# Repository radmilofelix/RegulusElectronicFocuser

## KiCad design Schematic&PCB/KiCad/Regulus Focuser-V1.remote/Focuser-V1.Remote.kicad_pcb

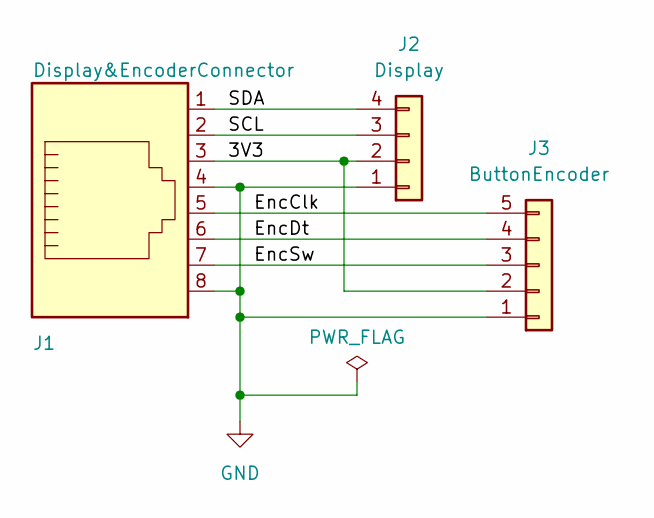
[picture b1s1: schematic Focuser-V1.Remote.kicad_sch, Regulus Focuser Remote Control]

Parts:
J1: Display&EncoderConnector; RJ45_Amphenol_54602-x08_Horizontal
J2: Display; PinHeader_1x04_P2.54mm_Vertical
J3: ButtonEncoder; PinHeader_1x05_P2.54mm_Vertical

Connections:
/3V3: J1.3, J2.2, J3.2
/EncClk: J1.5, J3.5
/EncDt: J1.6, J3.4
/EncSw: J1.7, J3.3
/SCL: J1.2, J2.3
/SDA: J1.1, J2.4
GND: J1.4, J1.8, J2.1, J3.1

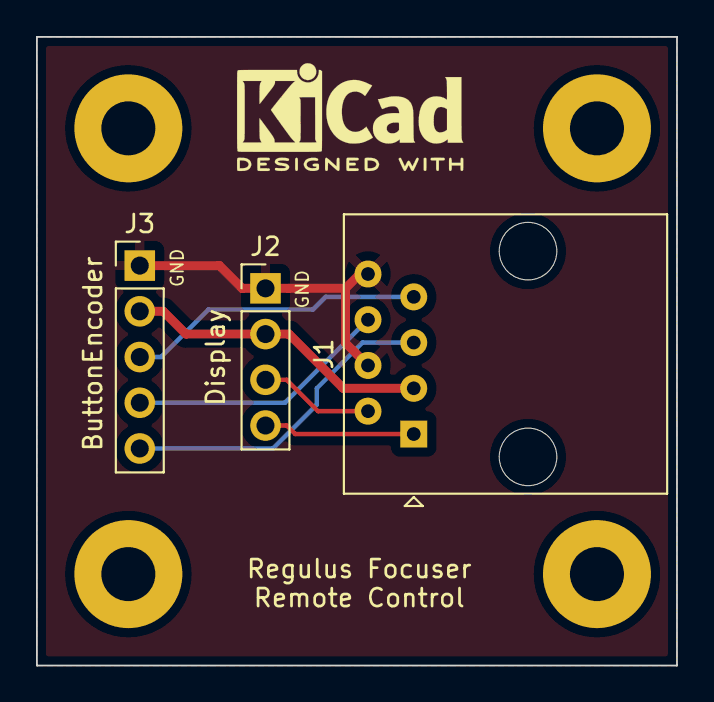
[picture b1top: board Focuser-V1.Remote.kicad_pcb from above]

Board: 2 copper layers, 35.6 x 34.9 mm, 7 parts (0 on the bottom side), 7 nets.

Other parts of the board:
REF1, REF2, REF3, REF4: MountingHole_3mm_Pad

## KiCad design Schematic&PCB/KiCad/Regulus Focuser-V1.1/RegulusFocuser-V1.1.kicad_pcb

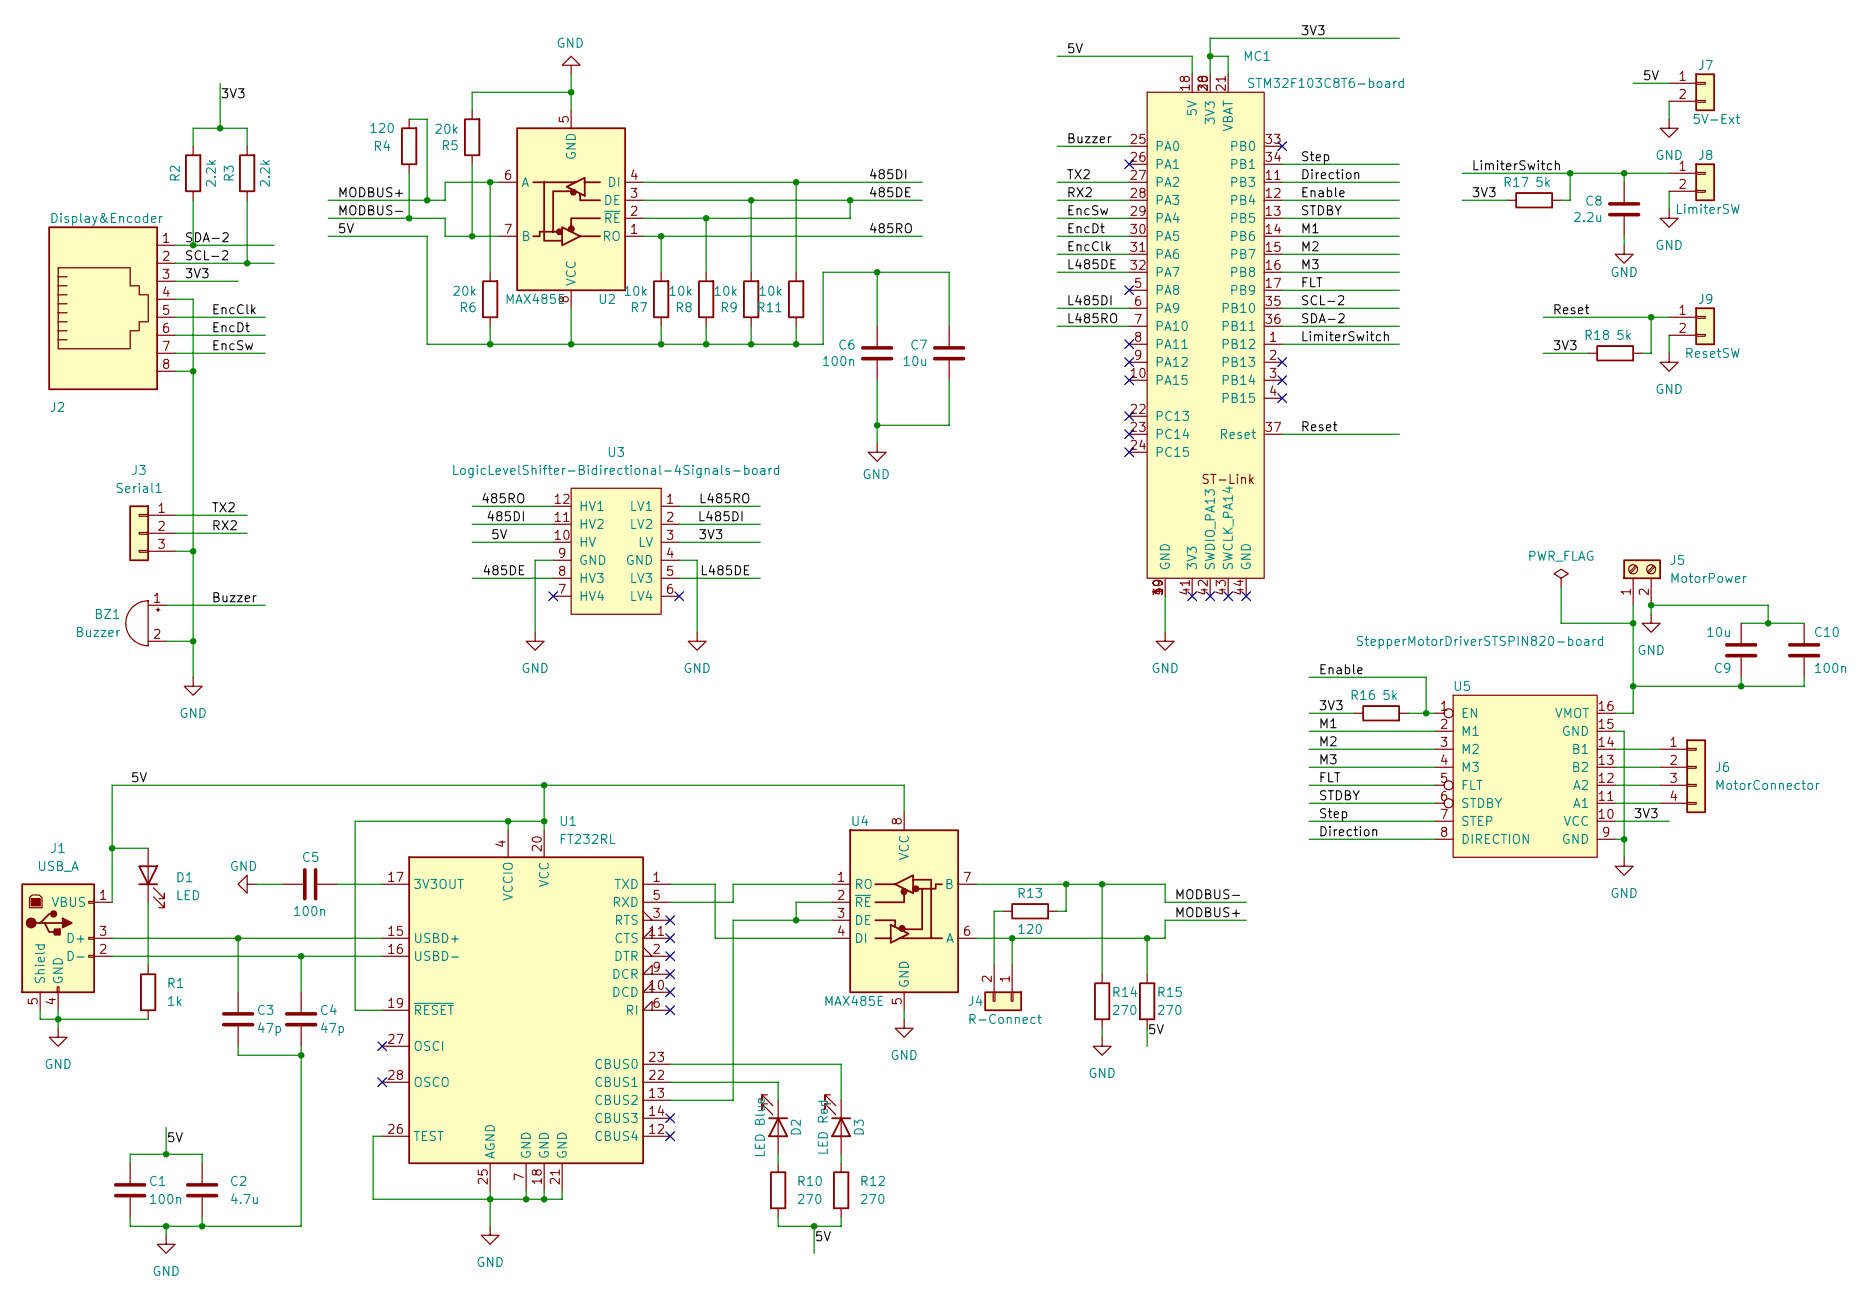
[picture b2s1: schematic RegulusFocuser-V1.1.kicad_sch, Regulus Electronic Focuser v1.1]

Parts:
BZ1: Buzzer; Buzzer-HSD-4pin
C1, C5, C6, C10: 100n; C_0805_2012Metric; LCSC C49678
C2: 4.7u; C_0805_2012Metric; LCSC C1779
C3, C4: 47p; C_0805_2012Metric; LCSC C14857
C7, C9: 10u; CP_EIA-3528-21_Kemet-B; LCSC C140404
C8: 2.2u; C_0805_2012Metric; LCSC C49217
D1: LED; LED_1206_3216Metric; LCSC C84270
D2: LED Blue; LED_0603_1608Metric; LCSC C84266
D3: LED Red; LED_0603_1608Metric; LCSC C2286
J1: USB_A; USB_B_Lumberg_2411_02_Horizontal
J2: Display&Encoder; RJ45_Amphenol_54602-x08_Horizontal
J3: Serial1; PinHeader_1x03_P2.54mm_Vertical
J4: R-Connect; PinHeader_1x02_P2.54mm_Vertical
J5: MotorPower; TerminalBlock_PTR_AKZ950-2_P5.08mm_Vertical
J6: MotorConnector; PinHeader_1x04_P2.54mm_Vertical
J7: 5V-Ext; PinHeader_1x02_P2.54mm_Vertical
J8: LimiterSW; PinHeader_1x02_P2.54mm_Vertical
J9: ResetSW; PinHeader_1x02_P2.54mm_Vertical
MC1: STM32F103C8T6-board; STM32F103C8T6
R1: 1k; R_1206_3216Metric; LCSC C136873
R2, R3: 2.2k; R_1206_3216Metric; LCSC C325909
R4, R13: 120; R_1206_3216Metric; LCSC C175512
R5, R6: 20k; R_1206_3216Metric; LCSC C18003
R7, R8, R9, R11: 10k; R_1206_3216Metric; LCSC C269766
R10, R12, R14, R15: 270; R_1206_3216Metric; LCSC C25366
R16, R17, R18: 5k; R_1206_3216Metric; LCSC C327044
U1: FT232RL; SSOP-28_5.3x10.2mm_P0.65mm; LCSC C8690
U2, U4: MAX485E; SOIC-8_3.9x4.9mm_P1.27mm; LCSC C19738
U3: LogicLevelShifter-Bidirectional-4Signals-board; LogicLevelShifter_Bidirectional_4Signals
U5: StepperMotorDriverSTSPIN820-board; StepperMotorDriverSTSPIN820

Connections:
/3V3: J2.3, MC1.20 (3V3), MC1.21 (VBAT), MC1.38 (3V3), R2.2, R3.2, R16.1, R17.1, R18.1, U3.3 (LV), U5.10 (VCC)
/5V: C1.1, C2.1, C6.1, C7.1, D1.2 (A), J1.1 (VBUS), J7.1, MC1.18 (5V), R6.1, R7.1, R8.1, R9.1, R10.2, R11.1, R12.2, R15.2, U1.4 (VCCIO), U1.19 (~RESET), U1.20 (VCC), U2.8 (VCC), U3.10 (HV), U4.8 (VCC)
/485DE: R8.2, R9.2, U2.2 (~RE), U2.3 (DE), U3.8 (HV3)
/485DI: R11.2, U2.4 (DI), U3.11 (HV2)
/485RO: R7.2, U2.1 (RO), U3.12 (HV1)
/Buzzer: BZ1.1 (-), MC1.25 (PA0)
/Direction: MC1.11 (PB3), U5.8 (DIRECTION)
/Enable: MC1.12 (PB4), R16.2, U5.1 (EN)
/EncClk: J2.5, MC1.31 (PA6)
/EncDt: J2.6, MC1.30 (PA5)
/EncSw: J2.7, MC1.29 (PA4)
/FLT: MC1.17 (PB9), U5.5 (FLT)
/L485DE: MC1.32 (PA7), U3.5 (LV3)
/L485DI: MC1.6 (PA9), U3.2 (LV2)
/L485RO: MC1.7 (PA10), U3.1 (LV1)
/LimiterSwitch: C8.1, J8.1, MC1.1 (PB12), R17.2
/M1: MC1.14 (PB6), U5.2 (M1)
/M2: MC1.15 (PB7), U5.3 (M2)
/M3: MC1.16 (PB8), U5.4 (M3)
/MODBUS+: J4.1, R4.2, R6.2, R15.1, U2.6 (A), U4.6 (A)
/MODBUS-: R4.1, R5.1, R13.2, R14.1, U2.7 (B), U4.7 (B)
/RX2: J3.2, MC1.28 (PA3)
/Reset: J9.1, MC1.37 (Reset), R18.2
/SCL-2: J2.2, MC1.35 (PB10), R3.1
/SDA-2: J2.1, MC1.36 (PB11), R2.1
/STDBY: MC1.13 (PB5), U5.6 (STDBY)
/Step: MC1.34 (PB1), U5.7 (STEP)
/TX2: J3.1, MC1.27 (PA2)
GND: BZ1.2 (+), C1.2, C2.2, C3.2, C4.2, C5.2, C6.2, C7.2, C8.2, C9.2, C10.1, J1.4 (GND), J1.5 (Shield), J2.4, J2.8, J3.3, J5.2, J7.2, J8.2, J9.2, MC1.19 (GND), MC1.39 (GND), MC1.40 (GND), R1.2, R5.2, R14.2, U1.7 (GND), U1.18 (GND), U1.21 (GND), U1.25 (AGND), U1.26 (TEST), U2.5 (GND), U3.4 (GND), U3.9 (GND), U4.5 (GND), U5.9 (GND), U5.15 (GND)
unnamed: D1.1 (K), R1.1
unnamed: D2.2 (A), R10.1
unnamed: D2.1 (K), U1.22 (CBUS1)
unnamed: D3.2 (A), R12.1
unnamed: D3.1 (K), U1.23 (CBUS0)
unnamed: C3.1, J1.3 (D+), U1.15 (USBD+)
unnamed: C4.1, J1.2 (D-), U1.16 (USBD-)
unnamed: J4.2, R13.1
unnamed: C9.1, C10.2, J5.1, U5.16 (VMOT)
unnamed: J6.1, U5.14 (B1)
unnamed: J6.2, U5.13 (B2)
unnamed: J6.3, U5.12 (A2)
unnamed: J6.4, U5.11 (A1)
unnamed: C5.1, U1.17 (3V3OUT)
unnamed: U1.13 (CBUS2), U4.2 (~RE), U4.3 (DE)
unnamed: U1.5 (RXD), U4.1 (RO)
unnamed: U1.1 (TXD), U4.4 (DI)

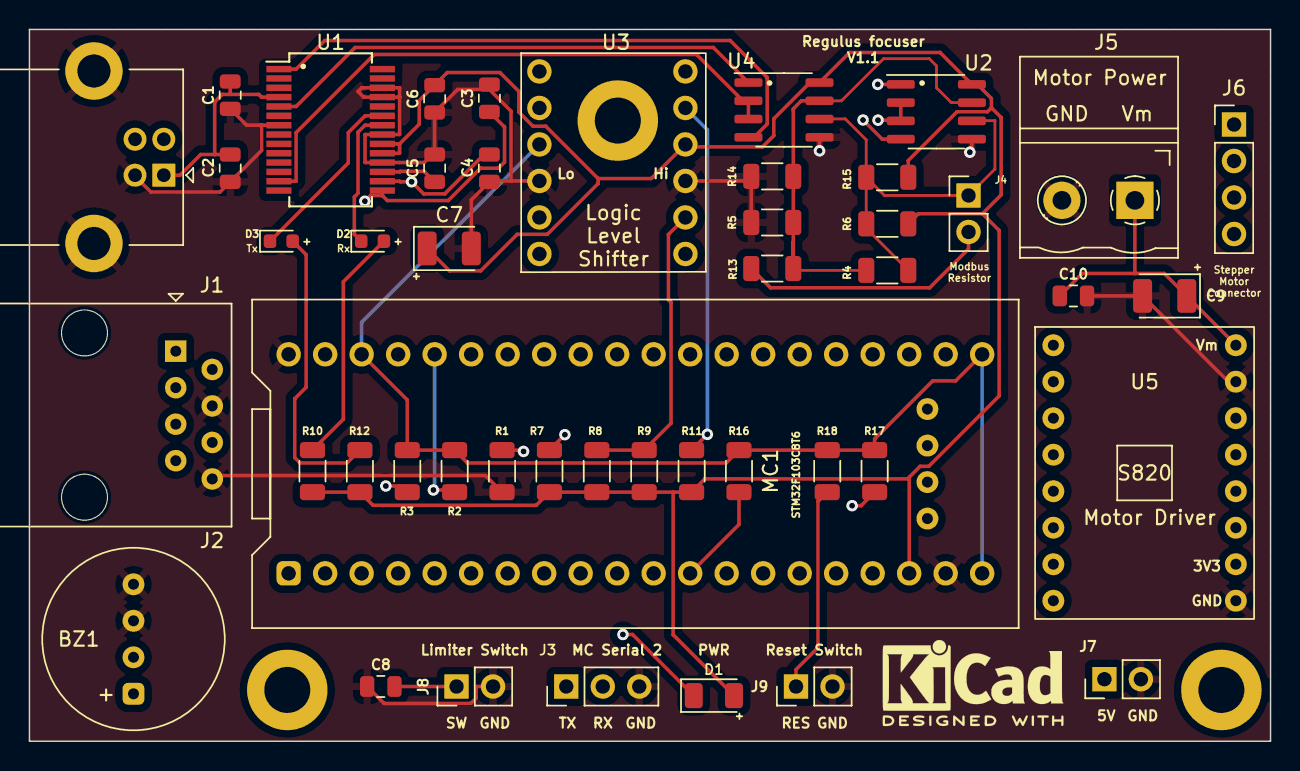
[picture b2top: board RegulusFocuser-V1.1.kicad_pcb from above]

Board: 4 copper layers, 86.4 x 49.5 mm, 50 parts (0 on the bottom side), 46 nets.

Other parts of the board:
MH1, MH2, MH3: MountingHole_3.2mm_M3_DIN965_Pad

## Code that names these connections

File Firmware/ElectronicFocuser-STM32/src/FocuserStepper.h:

#ifndef FOCUSERSTEPPER___H
#define FOCUSERSTEPPER___H

#include <Arduino.h>

// Travel distance: 17.5mm
// Travel distance per big wheel revolution: 13mm
// Steps per revolution (1/256 microstepping): 102400
// Total steps (1/256 microstepping): 138240
// Travel per step (1/256 microstepping): 126.953125nm

//#define FOCUSERDEBUG

#define EN  PB4     
#define M1  PB6 // A4988 MS1; DRV8825 M0; STSPIN220 MODE1; STSPIN820 M1       
#define M2  PB7 // A4988 MS2; DRV8825 M1; STSPIN220 MODE2; STSPIN820 M2 
#define M3  PB8 // A4988 MS3; DRV8825 M2; STSPIN220 (1); STSPIN820 M3 
#define STDBY  PB5
#define STEP  PB1
#define DIR  PB3
#define RESET PB5
#define TX2PIN PA2

#define DRIVERA4988 1
#define DRIVERDRV8825 2
#define DRIVERSTSPIN220 3
#define DRIVERSTSPIN820 4
#define LIMITSWITCHPIN PB12
#define LIMITSWITCHNORMALLYCLOSED
#define SAFETYMAXLIMDECREASEPERCENT 5
#define MAXGEAREDBACKLASH 100000

////////////////////////////////////////////////////////////////////////////////////////////////////
////////////////////////  Enable one of the focuser models
#define SCT_MCT
//#define PHOTON_254
//#define RACK_PINION_LO_PROFILE
////////////////////////////////////////////////////////////////////////////////////////////////////

#ifdef SCT_MCT
///////////////////////////////////////////////////////////////////////////////////////////////////////////////
////// Crayford 2 " Focuser for SCT & MCT - parameters
 #define FOCUSERTRAVEL 17 // mm
 #define FOCUSERTRAVELPER360 13 // mm
 #define GEARRATIO 1 // Direct drive
 #define MOTORRESOLUTION 1.8 // degrees per step
 #define MAXMICROSTEPPING 256
 #define GEAREDTYPE false
// UnscrewToRetract
///////////////////////////////////////////////////////////////////////////////////////////////////////////////
#endif

#ifdef PHOTON_254
////// Crayford 2 " Focuser for Newt. Photon 254 f:4 - parameters
 #define FOCUSERTRAVEL 50 // mm
 #define FOCUSERTRAVELPER360 13 // mm
 #define GEARRATIO 1 // Direct drive
 #define MOTORRESOLUTION 1.8 // degrees per step
 #define MAXMICROSTEPPING 256
 #define GEAREDTYPE false
// UnscrewToRetract
#endif

#ifdef RACK_PINION_LO_PROFILE
///////////////////////////////////////////////////////////////////////////////////////////////////////////////
////// Rack & Pinion low profile 2" focuser for Newtonians - parameters
 #define FOCUSERTRAVEL  23 // mm
 //#define FOCUSERTRAVEL  23 // mm
 #define FOCUSERTRAVELPER360 23 // mm
 #define GEARRATIO 100 // 
 #define MOTORRESOLUTION 1.8 // degrees per step
 #define MAXMICROSTEPPING 256
 #define GEAREDTYPE true
 // UnscrewToRetract
///////////////////////////////////////////////////////////////////////////////////////////////////////////////
#endif


///////////////////////////////////////////////////////////////////////////////////////////////////////////////
class FocuserStepper
{
    public:
    FocuserStepper();
    ~FocuserStepper();
	int PulseStep (uint32_t numberOfSteps, int motionDirection, int duration);
	void PulseStepToTarget ();
	void RelativePulseStepToTarget(uint32_t relativeSteps);
	int ToneStep (uint32_t numberOfSteps, int motionDirection, uint32_t frequency);
	void SelectMicrostepMode(int microstep);
	void ValidateMicrostepMode();
	void EnableMotor(bool value);
	void SetMotorDirection(int direction);
	void SetFocuserSpeed(int index);
	void CorrelateSpeed(uint32_t numberOfSteps);
	
	int motorDirection; // -1 = retract; 1 = extend
	int coilConfiguration; // 1 = normal; 2 = reversed
	bool motorEnable;
	uint32_t steps;
	uint32_t freq;
	int halfCycleDuration; // step half cycle duration in microseconds
	int microstepping;
	int ms1;
	int ms2;
	int ms3;
	int tempdir,tempstep;
	int motorDriver;

	int speedIndex; // index for focuser speeds
	int optimalSpeed; // optimal maximal speed to be used
	long stepPosition; // focuser position in steps
	long stepTarget; // target position for focuser
	long stepRate; // number of step per encoder tick
    bool gearedType;
    int backlash;
	uint32_t maxSteps; // maximal number of steps in use
	uint32_t maxStepsAbsolute; // maximum steps calculated from FOCUSERTRAVEL, FOCUSERTRAVELPER360, MOTORRESOLUTION, MAXMICROSTEPPING and GEARRATIO values
};

#endif

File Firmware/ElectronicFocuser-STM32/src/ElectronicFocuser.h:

//#include <Arduino.h>
#include "ModbusSlave.h"
#include <Adafruit_SSD1306.h>
#include <RotaryEncoder.h>
#include "OneButton.h"
#include "FocuserStepper.h"
#include "FocuserDefinitions.h"

//#define DEBUG

#define ENCODER_CLK PA6
#define ENCODER_DT PA5
#define ENCODER_SW  PA4
#define BUZZERPIN PA0

#define SCREEN_WIDTH 128 // OLED display width, in pixels
#define SCREEN_HEIGHT 64 // OLED display height, in pixels

//  Use I2C-1
//Adafruit_SSD1306 display(SCREEN_WIDTH, SCREEN_HEIGHT, &Wire, -1);

//  Use I2C-2
TwoWire Wire1(PB11, PB10);// Use STM32 I2C2
Adafruit_SSD1306 display(SCREEN_WIDTH, SCREEN_HEIGHT, &Wire1, -1);
HardwareSerial Serial2(USART2);   // PA3  (RX)  PA2  (TX)

void setup();
void loop();
void LimitSwitchInterrupt();
void BacklashInterrupt();
void MotorInit();
void FocuserInit(int initMode);
void SyncToZero();
uint32_t Get32FromFlash();
void Set32ToFlash();
void GetFlashFault();
void SetFlashFault(byte faultValue);
void GetFlashPosition();
void SetFlashPosition(uint32_t positionValue);
void GetFlashBacklash();
void SetFlashBacklash(uint32_t backlashValue);
void FindZero();
void WaitForBacklashSwitchClick();
void BacklashTravel(int travelspeed, uint32_t travelTarget);
void BacklashDetect(int travelspeed, uint32_t travelTarget);


#ifdef DEBUG
void DisplayMenu();
void DisplayFocuserData();
unsigned uint32_t ReadNumber();
void DisplayValues();
void KeyboardOperationSelect();
#endif


///////////////////////////////////////////////////////// Messages & Beeps /////////////////////////////////////////////////////
void Signal2Beep1();
void Signal2Beep2();
void SignalBeep1();
void SignalBeep2();
void SignalBeep3();
void SignalBeeps(int nbeeps, int beepFreq);

void DisplayRefresh();
void DisplayMessageRegulusFocuser();
void DisplayMessageInitStartMessage();
void DisplayMessageRegulusFocuserInit();
void DisplayMessageInitStage1();
void DisplayMessageInitCanNotReachZero();
void DisplayMessageInitStage2();
void DisplayMessageInitCanNotReachMax();
void DisplayMessageInitStage3();
void DisplayMessageInitEarlyZero();
void DisplayMessageFocuserFault();
void DisplayMessageClearFocuserFault();
void DisplayMessageInitStage4();
void DisplayMessageInitStageFinalSlipError();
void DisplayMessageInitStageFinalBacklash();
void DisplayMessageSlipError();
void DisplayMessageInitErrorSlipping();
void DisplayMessageZeroSync();
void DisplayFocuserData();
void DisplayMessageBacklash(uint32_t backlash);
void DisplayMessageBacklashAid1();
void DisplayMessageBacklashAid2();
void DisplayMessageBacklashWaitForInput();
void DisplayMessageBacklashReversing();
void DisplayMessageBacklashDetectionFinished();
void DisplayMessageBacklashDetected(uint32_t value);
void DisplayMessageBacklashMeasurements(uint32_t value1, uint32_t value2, uint32_t value3, uint32_t value4);
////////////////////////////////////////////////////////////////////////////////////////////////////////////////////////////////

///////////////////////////////////////////////// Encoder callbacks /////////////////////////////////////////////////////////////
void CheckTicks();
void SingleClick();
void DoubleClick();
void MultiClick();
void PressStart();
void PressStop();
static int pos = 0;
/////////////////////////////////////////////////////////////////////////////////////////////////////////////////////////////////

void ModbusPoll();
void CommandProcessor();
void BacklashAid();

bool notInit = true;
bool interruptTriggered = false;
//bool remoteControlEnabled = false;
bool remoteControlEnabled = true;
bool backlashInterruptEnable=false;
bool longPress=false;
byte focuserFault = 0;
uint32_t flashPosition;
uint32_t backlash = 0;
uint32_t PressStartTime, cycleTime;
int longClickCycles=0;
int longClickCycleTime=100; // ms
uint32_t lostSteps; // step difference when focuser hits the limit switch at 0 position
int working=0;
unsigned int previousPress = 0;
unsigned int previousBouncePress = 0;
int contactDebounce = 400;
int variableTextSize = 2;
int slipError;
//bool SingleClickToBacklash = false;

RotaryEncoder *encoder = nullptr;
OneButton button(ENCODER_SW, true);
ModbusSlave modbus_f(1,Serial1,PA7);
FocuserStepper fstepper;

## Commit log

2025-06-19 Code was adapted for the new INDI library v2.1.4, CMakeLists.txt optimised
2026-03-08 Added backlash aid in firmware
2026-03-22 Fix modbus poll dimension error
